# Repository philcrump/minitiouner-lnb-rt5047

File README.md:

# minitiouner-lnb-rt5047

This is a PCB for a 13V/18V LNB Bias Voltage supply, designed to be used with the Minitiouner V2 hardware. A single regulator is present however this can easily supply 100mA LNBs on both channels.

Inputs are available for Enable/Disable, and 13V/18V selection. An output for a "Fault" LED indicator is also available.

22KHz tone feature requires an external modulator, an input is available for this, however it has not been tested by the author.

[Schematic PDF file](https://github.com/philcrump/minitiouner-lnb-rt5047/raw/master/minitiouner-rt5047.pdf)

## PCB Images

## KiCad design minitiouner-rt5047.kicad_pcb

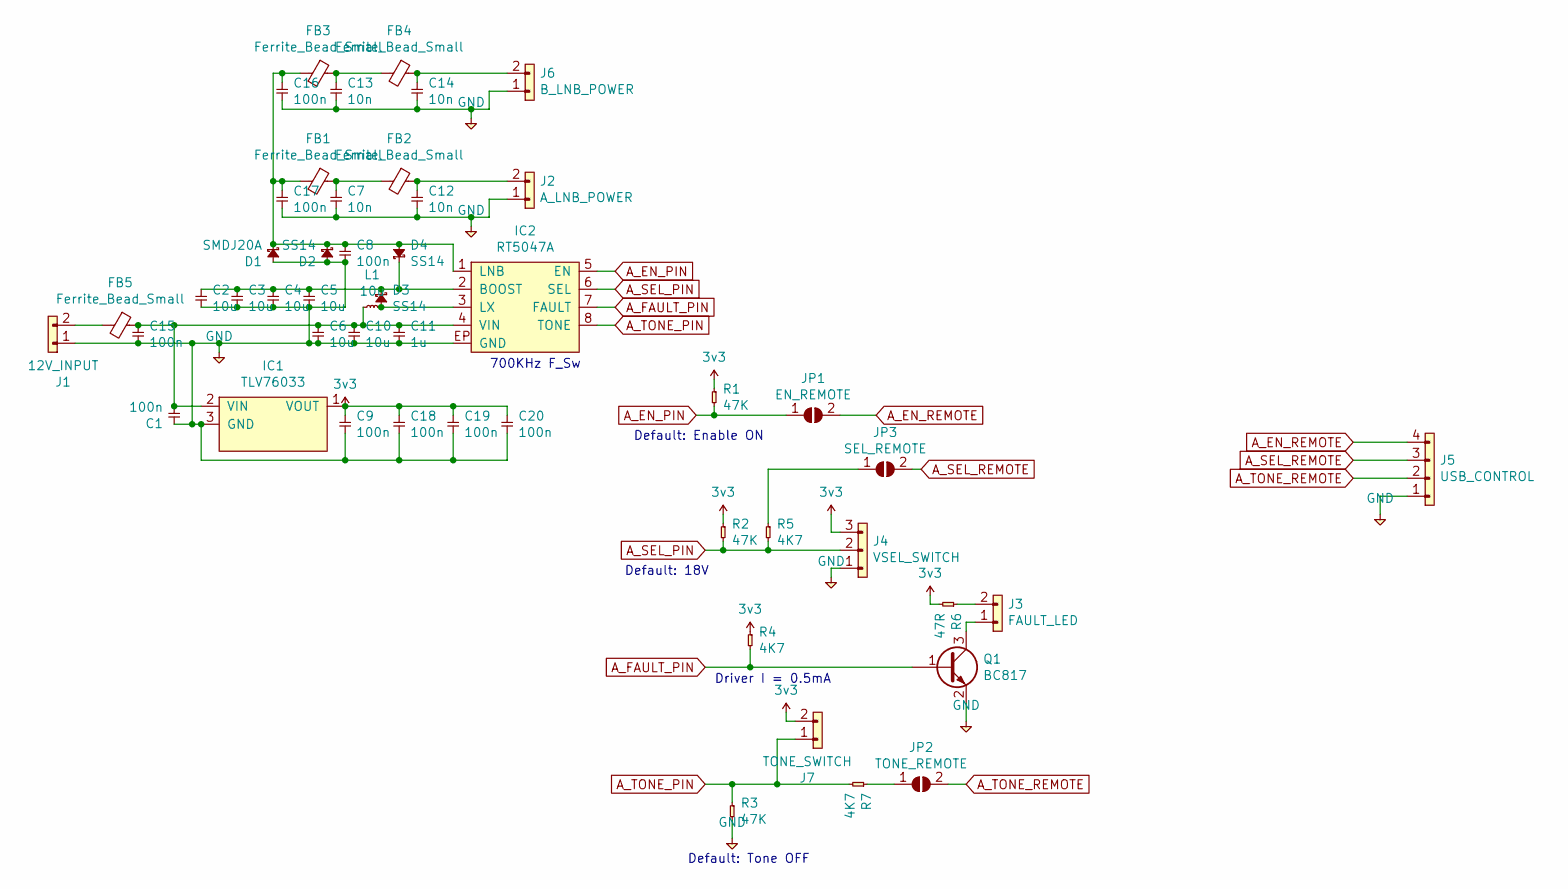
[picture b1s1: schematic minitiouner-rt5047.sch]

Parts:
C1, C8, C9, C15, C16, C17, C18, C19, C20: 100n; 0603
C2, C3, C4, C5, C6, C10: 10u; 0805
C7, C12, C13, C14: 10n; 0603
C11: 1u; 0603
D1: SMDJ20A; DO-214AB-SMC; Farnell 2777300
D2, D3, D4: SS14; DO-214AC-SMA
FB1, FB2, FB3, FB4, FB5: Ferrite_Bead_Small; 0805; FARNELL 2859031
IC1: TLV76033; SOT-23; Farnell 2773545
IC2: RT5047A; SOIC-8-EP; Farnell 2545957
J1: 12V_INPUT; Molex_KK-254_AE-6410-02A_1x02_P2.54mm_Vertical
J2: A_LNB_POWER; Molex_KK-254_AE-6410-02A_1x02_P2.54mm_Vertical
J3: FAULT_LED; Molex_KK-254_AE-6410-02A_1x02_P2.54mm_Vertical
J4: VSEL_SWITCH; Molex_KK-254_AE-6410-03A_1x03_P2.54mm_Vertical
J5: USB_CONTROL; Molex_KK-254_AE-6410-04A_1x04_P2.54mm_Vertical
J6: B_LNB_POWER; Molex_KK-254_AE-6410-02A_1x02_P2.54mm_Vertical
J7: TONE_SWITCH; Molex_KK-254_AE-6410-02A_1x02_P2.54mm_Vertical
JP1: EN_REMOTE; SolderJumper-2_P1.3mm_Open_Pad1.0x1.5mm
JP2: TONE_REMOTE; SolderJumper-2_P1.3mm_Open_Pad1.0x1.5mm
JP3: SEL_REMOTE; SolderJumper-2_P1.3mm_Open_Pad1.0x1.5mm
L1: 10u; L_Bourns_SRN6045TA; FARNELL 2061652
Q1: BC817; SOT-23; FARNELL 1902482
R1, R2, R3: 47K; 0603
R4, R5, R7: 4K7; 0603
R6: 47R; 0603

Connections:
3v3: C9.1, C18.1, C19.1, C20.1, IC1.1 (VOUT), J4.3, J7.2, R1.1, R2.1, R4.1, R6.2
A_EN_PIN: IC2.5 (EN), JP1.1 (A), R1.2
A_EN_REMOTE: J5.4, JP1.2 (B)
A_FAULT_PIN: IC2.7 (FAULT), Q1.1 (B), R4.2
A_SEL_PIN: IC2.6 (SEL), J4.2, R2.2, R5.2
A_SEL_REMOTE: J5.3, JP3.2 (B)
A_TONE_PIN: IC2.8 (TONE), J7.1, R3.1, R7.2
A_TONE_REMOTE: J5.2, JP2.2 (B)
GND: C1.1, C2.2, C3.2, C4.2, C5.2, C6.2, C7.2, C8.2, C9.2, C10.2, C11.2, C12.2, C13.2, C14.2, C15.2, C16.2, C17.2, C18.2, C19.2, C20.2, D1.2, D2.2, IC1.3 (GND), IC2.EP (GND), J1.1, J2.1, J4.1, J5.1, J6.1, Q1.2 (E), R3.2
unnamed: C1.2, C6.1, C10.1, C11.1, C15.1, FB5.1, IC1.2 (VIN), IC2.4 (VIN), L1.1
unnamed: C2.1, C3.1, C4.1, C5.1, D3.1, D4.1, IC2.2 (BOOST)
unnamed: C7.1, FB1.1, FB2.2
unnamed: C12.1, FB2.1, J2.2
unnamed: C13.1, FB3.1, FB4.2
unnamed: C14.1, FB4.1, J6.2
unnamed: C8.1, C16.1, C17.1, D1.1, D2.1, D4.2, FB1.2, FB3.2, IC2.1 (LNB)
unnamed: D3.2, IC2.3 (LX), L1.2
unnamed: FB5.2, J1.2
unnamed: J3.1, Q1.3 (C)
unnamed: J3.2, R6.1
unnamed: JP2.1 (A), R7.1
unnamed: JP3.1 (A), R5.1

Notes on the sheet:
Driver I = 0.5mA
700KHz F_Sw
Default: Tone OFF
Default: Enable ON
Default: 18V

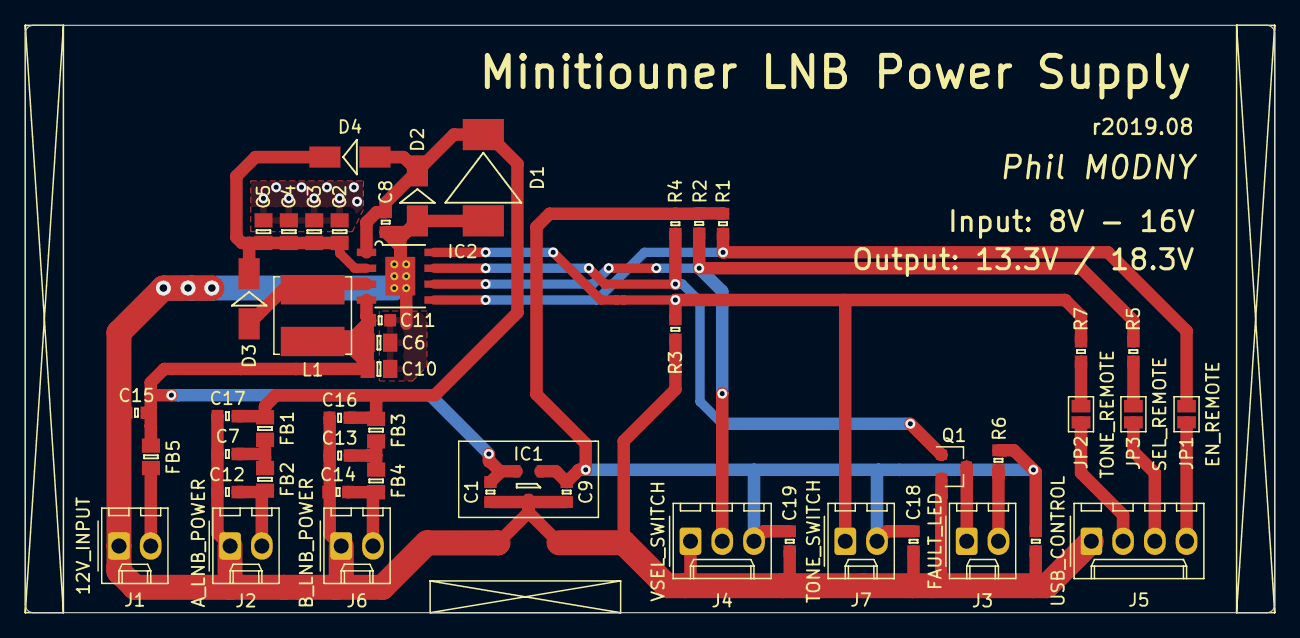
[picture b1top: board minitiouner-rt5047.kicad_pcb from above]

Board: 2 copper layers, 99.9 x 47.0 mm, 50 parts (0 on the bottom side), 22 nets.

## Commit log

2019-08-20 Initial commit (add lib/agg)
2019-08-20 Start sch.
2019-09-04 WIP.
2019-12-28 Add gitignore.
2019-12-28 Remove erroneously committed files.
2019-12-28 Update to correct philcrump/agg-kicad ref.
2019-12-28 Add final changes and fabrication output.
2019-12-28 Add LICENSE
2019-12-28 Add schematic, top & bottom pcb; renders.
2019-12-29 Add README.
